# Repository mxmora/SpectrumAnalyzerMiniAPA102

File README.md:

# SpectrumAnalyzerMiniAPA102
SpectrumAnalyzerMiniAPA102

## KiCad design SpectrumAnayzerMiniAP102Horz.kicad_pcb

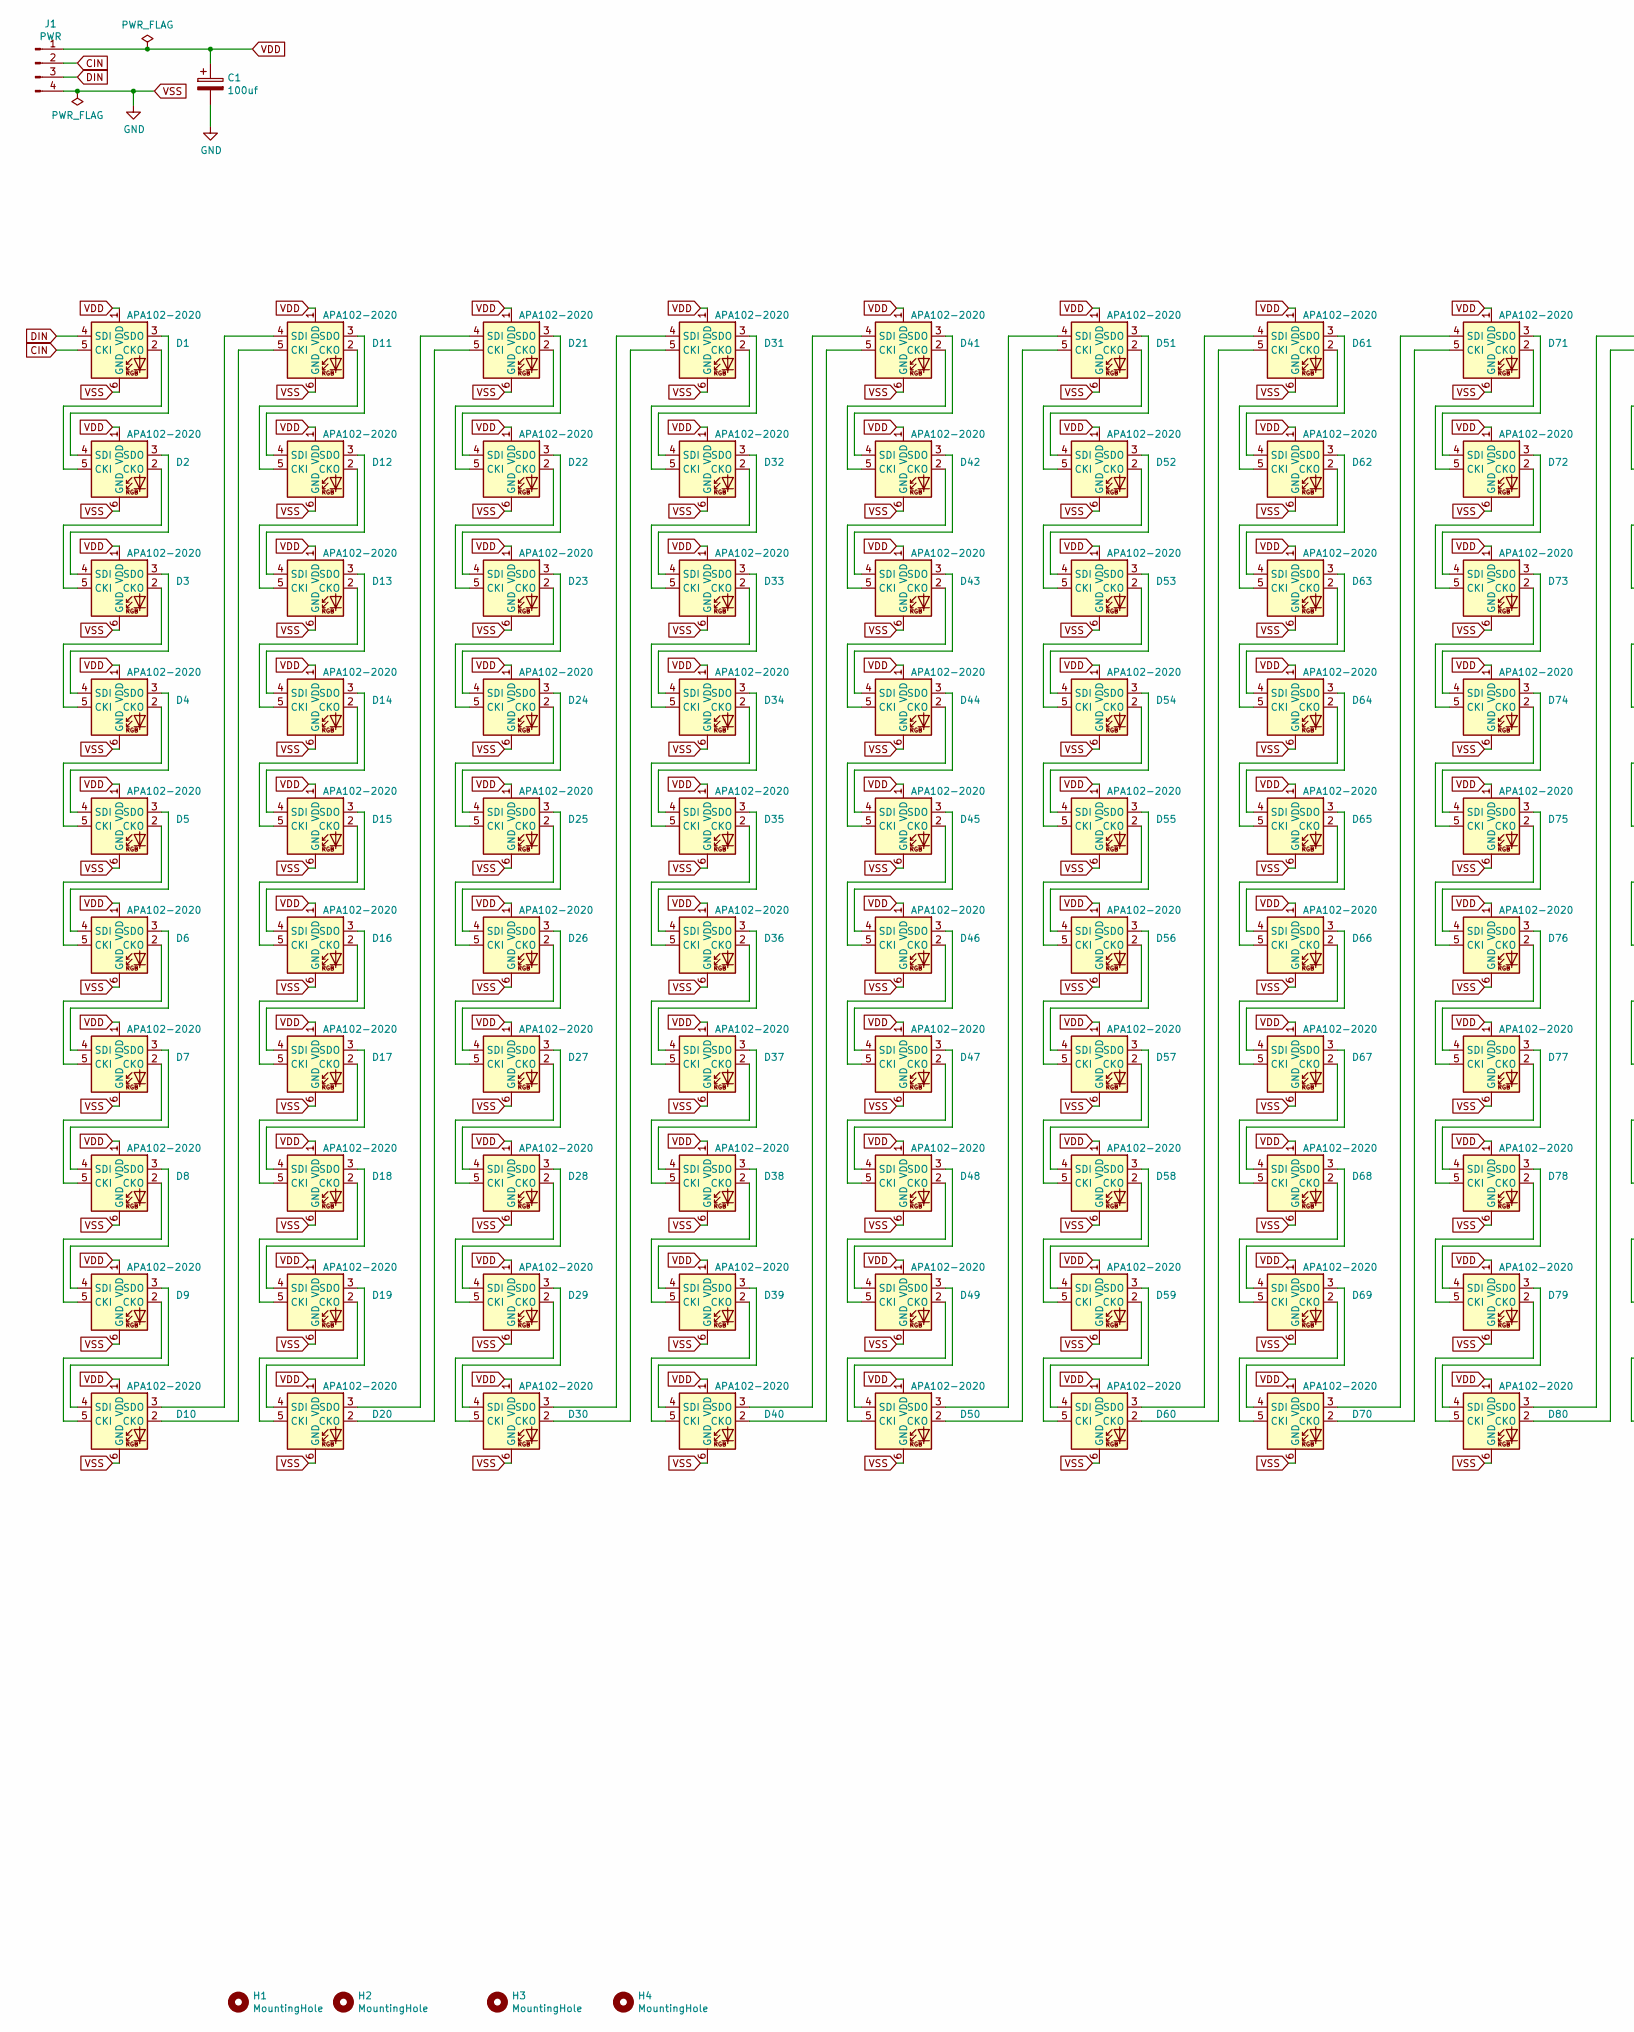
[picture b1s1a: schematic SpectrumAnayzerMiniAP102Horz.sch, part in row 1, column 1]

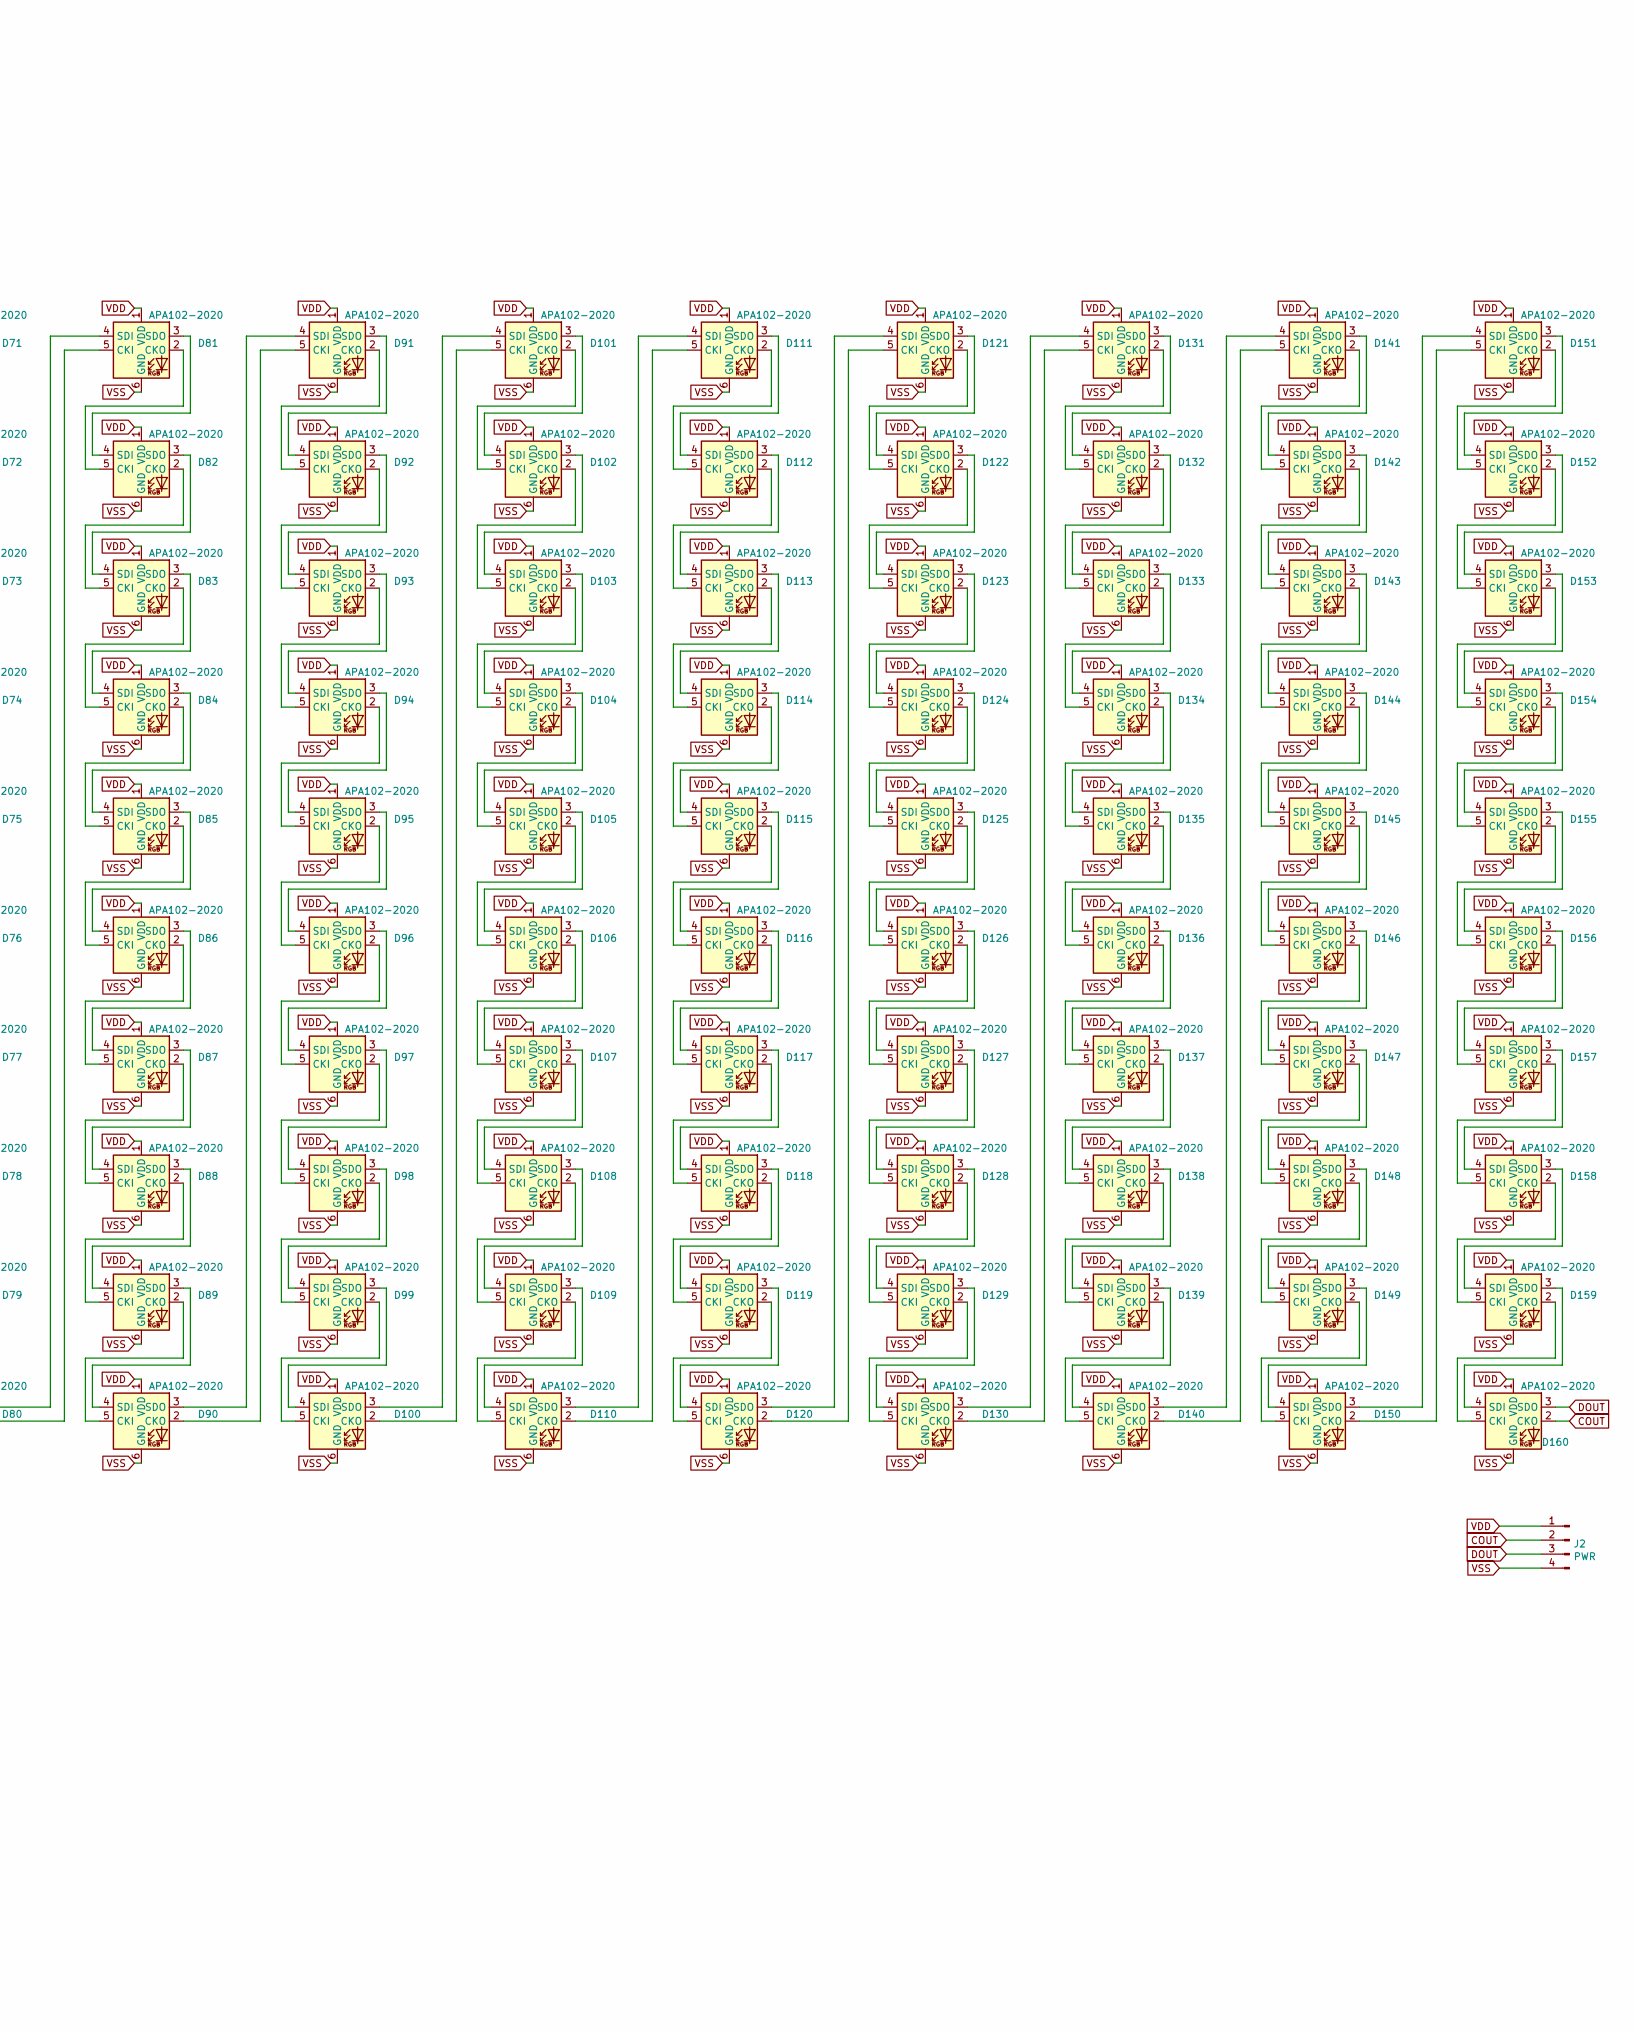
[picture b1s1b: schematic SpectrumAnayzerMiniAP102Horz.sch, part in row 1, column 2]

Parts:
C1: 100uf; CP_Radial_D5.0mm_P2.50mm
D1, D11, D21, D31, D41, D51, D61, D71, D81, D91, D101, D111, D121, D131, D141, D151: APA102-2020; LED-APA102-2020; LCSC C114586
D2, D3, D4, D5, D6, D7, D8, D9, D10, D12, D13, D14, D15, D16, D17, D18, D19, D20, D22, D23, D24, D25, D26, D27, D28, D29, D30, D32, D33, D34, D35, D36, D37, D38, D39, D40, D42, D43, D44, D45, D46, D47, D48, D49, D50, D52, D53, D54, D55, D56, D57, D58, D59, D60, D62, D63, D64, D65, D66, D67, D68, D69, D70, D72, D73, D74, D75, D76, D77, D78, D79, D80, D82, D83, D84, D85, D86, D87, D88, D89, D90, D92, D93, D94, D95, D96, D97, D98, D99, D100, D102, D103, D104, D105, D106, D107, D108, D109, D110, D112, D113, D114, D115, D116, D117, D118, D119, D120, D122, D123, D124, D125, D126, D127, D128, D129, D130, D132, D133, D134, D135, D136, D137, D138, D139, D140, D142, D143, D144, D145, D146, D147, D148, D149, D150, D152, D153, D154, D155, D156, D157, D158, D159, D160: APA102-2020; LED-APA102-2020
H1, H2, H3, H4: MountingHole; MountingHole_2.5mm
J1, J2: PWR; PinHeader_1x04_P2.54mm_Vertical

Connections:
CIN: D1.5 (CKI), J1.2
COUT: D160.2 (CKO), J2.2
DIN: D1.4 (SDI), J1.3
DOUT: D160.3 (SDO), J2.3
unnamed: D1.2 (CKO), D2.5 (CKI)
unnamed: D1.3 (SDO), D2.4 (SDI)
unnamed: D2.2 (CKO), D3.5 (CKI)
unnamed: D2.3 (SDO), D3.4 (SDI)
unnamed: D3.2 (CKO), D4.5 (CKI)
unnamed: D3.3 (SDO), D4.4 (SDI)
unnamed: D4.2 (CKO), D5.5 (CKI)
unnamed: D4.3 (SDO), D5.4 (SDI)
unnamed: D5.2 (CKO), D6.5 (CKI)
unnamed: D5.3 (SDO), D6.4 (SDI)
unnamed: D6.2 (CKO), D7.5 (CKI)
unnamed: D6.3 (SDO), D7.4 (SDI)
unnamed: D7.2 (CKO), D8.5 (CKI)
unnamed: D7.3 (SDO), D8.4 (SDI)
unnamed: D8.2 (CKO), D9.5 (CKI)
unnamed: D8.3 (SDO), D9.4 (SDI)
unnamed: D10.2 (CKO), D11.5 (CKI)
unnamed: D10.3 (SDO), D11.4 (SDI)
unnamed: D9.3 (SDO), D10.4 (SDI)
unnamed: D9.2 (CKO), D10.5 (CKI)
unnamed: D11.2 (CKO), D12.5 (CKI)
unnamed: D11.3 (SDO), D12.4 (SDI)
unnamed: D12.2 (CKO), D13.5 (CKI)
unnamed: D12.3 (SDO), D13.4 (SDI)
unnamed: D13.2 (CKO), D14.5 (CKI)
unnamed: D13.3 (SDO), D14.4 (SDI)
unnamed: D14.2 (CKO), D15.5 (CKI)
unnamed: D14.3 (SDO), D15.4 (SDI)
unnamed: D15.2 (CKO), D16.5 (CKI)
unnamed: D15.3 (SDO), D16.4 (SDI)
unnamed: D16.2 (CKO), D17.5 (CKI)
unnamed: D16.3 (SDO), D17.4 (SDI)
unnamed: D17.2 (CKO), D18.5 (CKI)
unnamed: D17.3 (SDO), D18.4 (SDI)
unnamed: D18.2 (CKO), D19.5 (CKI)
unnamed: D18.3 (SDO), D19.4 (SDI)
unnamed: D19.2 (CKO), D20.5 (CKI)
unnamed: D19.3 (SDO), D20.4 (SDI)
unnamed: D20.2 (CKO), D21.5 (CKI)
unnamed: D20.3 (SDO), D21.4 (SDI)
unnamed: D21.2 (CKO), D22.5 (CKI)
unnamed: D21.3 (SDO), D22.4 (SDI)
unnamed: D22.2 (CKO), D23.5 (CKI)
unnamed: D22.3 (SDO), D23.4 (SDI)
unnamed: D23.2 (CKO), D24.5 (CKI)
unnamed: D23.3 (SDO), D24.4 (SDI)
unnamed: D24.2 (CKO), D25.5 (CKI)
unnamed: D24.3 (SDO), D25.4 (SDI)
unnamed: D25.2 (CKO), D26.5 (CKI)
unnamed: D25.3 (SDO), D26.4 (SDI)
unnamed: D26.2 (CKO), D27.5 (CKI)
unnamed: D26.3 (SDO), D27.4 (SDI)
unnamed: D27.2 (CKO), D28.5 (CKI)
unnamed: D27.3 (SDO), D28.4 (SDI)
unnamed: D28.2 (CKO), D29.5 (CKI)
unnamed: D28.3 (SDO), D29.4 (SDI)
unnamed: D29.2 (CKO), D30.5 (CKI)
unnamed: D29.3 (SDO), D30.4 (SDI)
unnamed: D30.2 (CKO), D31.5 (CKI)
unnamed: D30.3 (SDO), D31.4 (SDI)
unnamed: D31.2 (CKO), D32.5 (CKI)
unnamed: D31.3 (SDO), D32.4 (SDI)
unnamed: D32.2 (CKO), D33.5 (CKI)
unnamed: D32.3 (SDO), D33.4 (SDI)
unnamed: D33.2 (CKO), D34.5 (CKI)
unnamed: D33.3 (SDO), D34.4 (SDI)
unnamed: D34.2 (CKO), D35.5 (CKI)
unnamed: D34.3 (SDO), D35.4 (SDI)
unnamed: D35.2 (CKO), D36.5 (CKI)
unnamed: D35.3 (SDO), D36.4 (SDI)
unnamed: D36.2 (CKO), D37.5 (CKI)
unnamed: D36.3 (SDO), D37.4 (SDI)
unnamed: D37.2 (CKO), D38.5 (CKI)
unnamed: D37.3 (SDO), D38.4 (SDI)
unnamed: D38.2 (CKO), D39.5 (CKI)
unnamed: D38.3 (SDO), D39.4 (SDI)
unnamed: D39.2 (CKO), D40.5 (CKI)
unnamed: D39.3 (SDO), D40.4 (SDI)
unnamed: D40.2 (CKO), D41.5 (CKI)
unnamed: D40.3 (SDO), D41.4 (SDI)
unnamed: D41.2 (CKO), D42.5 (CKI)
unnamed: D41.3 (SDO), D42.4 (SDI)
unnamed: D42.2 (CKO), D43.5 (CKI)
unnamed: D42.3 (SDO), D43.4 (SDI)
unnamed: D43.2 (CKO), D44.5 (CKI)
unnamed: D43.3 (SDO), D44.4 (SDI)
unnamed: D44.2 (CKO), D45.5 (CKI)
unnamed: D44.3 (SDO), D45.4 (SDI)
unnamed: D45.2 (CKO), D46.5 (CKI)
unnamed: D45.3 (SDO), D46.4 (SDI)
unnamed: D46.2 (CKO), D47.5 (CKI)
unnamed: D46.3 (SDO), D47.4 (SDI)
unnamed: D47.2 (CKO), D48.5 (CKI)
unnamed: D47.3 (SDO), D48.4 (SDI)
unnamed: D48.2 (CKO), D49.5 (CKI)
unnamed: D48.3 (SDO), D49.4 (SDI)
unnamed: D49.2 (CKO), D50.5 (CKI)
unnamed: D49.3 (SDO), D50.4 (SDI)
unnamed: D50.2 (CKO), D51.5 (CKI)
unnamed: D50.3 (SDO), D51.4 (SDI)
unnamed: D51.2 (CKO), D52.5 (CKI)
unnamed: D51.3 (SDO), D52.4 (SDI)
unnamed: D52.2 (CKO), D53.5 (CKI)
unnamed: D52.3 (SDO), D53.4 (SDI)
unnamed: D53.2 (CKO), D54.5 (CKI)
unnamed: D53.3 (SDO), D54.4 (SDI)
unnamed: D54.2 (CKO), D55.5 (CKI)
unnamed: D54.3 (SDO), D55.4 (SDI)
unnamed: D55.2 (CKO), D56.5 (CKI)
unnamed: D55.3 (SDO), D56.4 (SDI)
unnamed: D56.2 (CKO), D57.5 (CKI)
unnamed: D56.3 (SDO), D57.4 (SDI)
unnamed: D57.2 (CKO), D58.5 (CKI)
unnamed: D57.3 (SDO), D58.4 (SDI)
unnamed: D58.2 (CKO), D59.5 (CKI)
unnamed: D58.3 (SDO), D59.4 (SDI)
unnamed: D59.2 (CKO), D60.5 (CKI)
unnamed: D59.3 (SDO), D60.4 (SDI)
unnamed: D60.2 (CKO), D61.5 (CKI)
unnamed: D60.3 (SDO), D61.4 (SDI)
unnamed: D61.2 (CKO), D62.5 (CKI)
unnamed: D61.3 (SDO), D62.4 (SDI)
unnamed: D62.2 (CKO), D63.5 (CKI)
unnamed: D62.3 (SDO), D63.4 (SDI)
unnamed: D63.2 (CKO), D64.5 (CKI)
unnamed: D63.3 (SDO), D64.4 (SDI)
unnamed: D64.2 (CKO), D65.5 (CKI)
unnamed: D64.3 (SDO), D65.4 (SDI)
unnamed: D65.2 (CKO), D66.5 (CKI)
unnamed: D65.3 (SDO), D66.4 (SDI)
unnamed: D66.2 (CKO), D67.5 (CKI)
unnamed: D66.3 (SDO), D67.4 (SDI)
unnamed: D67.2 (CKO), D68.5 (CKI)
unnamed: D67.3 (SDO), D68.4 (SDI)
unnamed: D68.2 (CKO), D69.5 (CKI)
unnamed: D68.3 (SDO), D69.4 (SDI)
unnamed: D69.2 (CKO), D70.5 (CKI)
unnamed: D69.3 (SDO), D70.4 (SDI)
unnamed: D70.2 (CKO), D71.5 (CKI)
unnamed: D70.3 (SDO), D71.4 (SDI)
unnamed: D71.2 (CKO), D72.5 (CKI)
unnamed: D71.3 (SDO), D72.4 (SDI)
unnamed: D72.2 (CKO), D73.5 (CKI)
unnamed: D72.3 (SDO), D73.4 (SDI)
unnamed: D73.2 (CKO), D74.5 (CKI)
unnamed: D73.3 (SDO), D74.4 (SDI)
unnamed: D74.2 (CKO), D75.5 (CKI)
unnamed: D74.3 (SDO), D75.4 (SDI)
unnamed: D75.2 (CKO), D76.5 (CKI)
unnamed: D75.3 (SDO), D76.4 (SDI)
unnamed: D76.2 (CKO), D77.5 (CKI)
unnamed: D76.3 (SDO), D77.4 (SDI)
unnamed: D77.2 (CKO), D78.5 (CKI)
unnamed: D77.3 (SDO), D78.4 (SDI)
unnamed: D78.2 (CKO), D79.5 (CKI)
unnamed: D78.3 (SDO), D79.4 (SDI)
unnamed: D79.2 (CKO), D80.5 (CKI)
unnamed: D79.3 (SDO), D80.4 (SDI)
unnamed: D80.2 (CKO), D81.5 (CKI)
unnamed: D80.3 (SDO), D81.4 (SDI)
unnamed: D81.2 (CKO), D82.5 (CKI)
unnamed: D81.3 (SDO), D82.4 (SDI)
unnamed: D82.2 (CKO), D83.5 (CKI)
unnamed: D82.3 (SDO), D83.4 (SDI)
unnamed: D83.2 (CKO), D84.5 (CKI)
unnamed: D83.3 (SDO), D84.4 (SDI)
unnamed: D84.2 (CKO), D85.5 (CKI)
unnamed: D84.3 (SDO), D85.4 (SDI)
unnamed: D85.2 (CKO), D86.5 (CKI)
unnamed: D85.3 (SDO), D86.4 (SDI)
unnamed: D86.2 (CKO), D87.5 (CKI)
unnamed: D86.3 (SDO), D87.4 (SDI)
unnamed: D87.2 (CKO), D88.5 (CKI)
unnamed: D87.3 (SDO), D88.4 (SDI)
unnamed: D88.2 (CKO), D89.5 (CKI)
unnamed: D88.3 (SDO), D89.4 (SDI)
unnamed: D89.2 (CKO), D90.5 (CKI)
unnamed: D89.3 (SDO), D90.4 (SDI)
unnamed: D90.2 (CKO), D91.5 (CKI)
unnamed: D90.3 (SDO), D91.4 (SDI)
unnamed: D91.2 (CKO), D92.5 (CKI)
unnamed: D91.3 (SDO), D92.4 (SDI)
unnamed: D92.2 (CKO), D93.5 (CKI)
unnamed: D92.3 (SDO), D93.4 (SDI)
unnamed: D93.2 (CKO), D94.5 (CKI)
unnamed: D93.3 (SDO), D94.4 (SDI)
unnamed: D94.2 (CKO), D95.5 (CKI)
unnamed: D94.3 (SDO), D95.4 (SDI)
unnamed: D95.2 (CKO), D96.5 (CKI)
unnamed: D95.3 (SDO), D96.4 (SDI)
unnamed: D96.2 (CKO), D97.5 (CKI)
unnamed: D96.3 (SDO), D97.4 (SDI)
unnamed: D97.2 (CKO), D98.5 (CKI)
unnamed: D97.3 (SDO), D98.4 (SDI)
unnamed: D98.2 (CKO), D99.5 (CKI)
unnamed: D98.3 (SDO), D99.4 (SDI)
unnamed: D100.2 (CKO), D101.5 (CKI)
unnamed: D100.3 (SDO), D101.4 (SDI)
unnamed: D99.3 (SDO), D100.4 (SDI)
unnamed: D99.2 (CKO), D100.5 (CKI)
unnamed: D101.2 (CKO), D102.5 (CKI)
unnamed: D101.3 (SDO), D102.4 (SDI)
unnamed: D102.2 (CKO), D103.5 (CKI)
unnamed: D102.3 (SDO), D103.4 (SDI)
unnamed: D103.2 (CKO), D104.5 (CKI)
unnamed: D103.3 (SDO), D104.4 (SDI)
unnamed: D104.2 (CKO), D105.5 (CKI)
unnamed: D104.3 (SDO), D105.4 (SDI)
unnamed: D105.2 (CKO), D106.5 (CKI)
unnamed: D105.3 (SDO), D106.4 (SDI)
unnamed: D106.2 (CKO), D107.5 (CKI)
unnamed: D106.3 (SDO), D107.4 (SDI)
unnamed: D107.2 (CKO), D108.5 (CKI)
unnamed: D107.3 (SDO), D108.4 (SDI)
unnamed: D108.2 (CKO), D109.5 (CKI)
unnamed: D108.3 (SDO), D109.4 (SDI)
unnamed: D109.2 (CKO), D110.5 (CKI)
unnamed: D109.3 (SDO), D110.4 (SDI)
unnamed: D110.2 (CKO), D111.5 (CKI)
unnamed: D110.3 (SDO), D111.4 (SDI)
unnamed: D111.2 (CKO), D112.5 (CKI)
unnamed: D111.3 (SDO), D112.4 (SDI)
unnamed: D112.2 (CKO), D113.5 (CKI)
unnamed: D112.3 (SDO), D113.4 (SDI)
unnamed: D113.2 (CKO), D114.5 (CKI)
unnamed: D113.3 (SDO), D114.4 (SDI)
unnamed: D114.2 (CKO), D115.5 (CKI)
unnamed: D114.3 (SDO), D115.4 (SDI)
unnamed: D115.2 (CKO), D116.5 (CKI)
unnamed: D115.3 (SDO), D116.4 (SDI)
unnamed: D116.2 (CKO), D117.5 (CKI)
unnamed: D116.3 (SDO), D117.4 (SDI)
unnamed: D117.2 (CKO), D118.5 (CKI)
unnamed: D117.3 (SDO), D118.4 (SDI)
unnamed: D118.2 (CKO), D119.5 (CKI)
unnamed: D118.3 (SDO), D119.4 (SDI)
unnamed: D119.2 (CKO), D120.5 (CKI)
unnamed: D119.3 (SDO), D120.4 (SDI)
unnamed: D120.2 (CKO), D121.5 (CKI)
unnamed: D120.3 (SDO), D121.4 (SDI)
unnamed: D121.2 (CKO), D122.5 (CKI)
unnamed: D121.3 (SDO), D122.4 (SDI)
unnamed: D122.2 (CKO), D123.5 (CKI)
unnamed: D122.3 (SDO), D123.4 (SDI)
unnamed: D123.2 (CKO), D124.5 (CKI)
unnamed: D123.3 (SDO), D124.4 (SDI)
unnamed: D124.2 (CKO), D125.5 (CKI)
unnamed: D124.3 (SDO), D125.4 (SDI)
unnamed: D125.2 (CKO), D126.5 (CKI)
unnamed: D125.3 (SDO), D126.4 (SDI)
unnamed: D126.2 (CKO), D127.5 (CKI)
unnamed: D126.3 (SDO), D127.4 (SDI)
unnamed: D127.2 (CKO), D128.5 (CKI)
unnamed: D127.3 (SDO), D128.4 (SDI)
unnamed: D128.2 (CKO), D129.5 (CKI)
unnamed: D128.3 (SDO), D129.4 (SDI)
unnamed: D129.2 (CKO), D130.5 (CKI)
unnamed: D129.3 (SDO), D130.4 (SDI)
unnamed: D130.2 (CKO), D131.5 (CKI)
unnamed: D130.3 (SDO), D131.4 (SDI)
unnamed: D131.2 (CKO), D132.5 (CKI)
unnamed: D131.3 (SDO), D132.4 (SDI)
unnamed: D132.2 (CKO), D133.5 (CKI)
unnamed: D132.3 (SDO), D133.4 (SDI)
unnamed: D133.2 (CKO), D134.5 (CKI)
unnamed: D133.3 (SDO), D134.4 (SDI)
unnamed: D134.2 (CKO), D135.5 (CKI)
unnamed: D134.3 (SDO), D135.4 (SDI)
unnamed: D135.2 (CKO), D136.5 (CKI)
unnamed: D135.3 (SDO), D136.4 (SDI)
unnamed: D136.2 (CKO), D137.5 (CKI)
unnamed: D136.3 (SDO), D137.4 (SDI)
unnamed: D137.2 (CKO), D138.5 (CKI)
unnamed: D137.3 (SDO), D138.4 (SDI)
unnamed: D138.2 (CKO), D139.5 (CKI)
unnamed: D138.3 (SDO), D139.4 (SDI)
unnamed: D139.2 (CKO), D140.5 (CKI)
unnamed: D139.3 (SDO), D140.4 (SDI)
unnamed: D140.2 (CKO), D141.5 (CKI)
unnamed: D140.3 (SDO), D141.4 (SDI)
unnamed: D141.2 (CKO), D142.5 (CKI)
unnamed: D141.3 (SDO), D142.4 (SDI)
unnamed: D142.2 (CKO), D143.5 (CKI)
unnamed: D142.3 (SDO), D143.4 (SDI)
unnamed: D143.2 (CKO), D144.5 (CKI)
unnamed: D143.3 (SDO), D144.4 (SDI)
unnamed: D144.2 (CKO), D145.5 (CKI)
unnamed: D144.3 (SDO), D145.4 (SDI)
unnamed: D145.2 (CKO), D146.5 (CKI)
unnamed: D145.3 (SDO), D146.4 (SDI)
unnamed: D146.2 (CKO), D147.5 (CKI)
unnamed: D146.3 (SDO), D147.4 (SDI)
unnamed: D147.2 (CKO), D148.5 (CKI)
unnamed: D147.3 (SDO), D148.4 (SDI)
unnamed: D148.2 (CKO), D149.5 (CKI)
unnamed: D148.3 (SDO), D149.4 (SDI)
unnamed: D149.2 (CKO), D150.5 (CKI)
unnamed: D149.3 (SDO), D150.4 (SDI)
unnamed: D150.2 (CKO), D151.5 (CKI)
unnamed: D150.3 (SDO), D151.4 (SDI)
unnamed: D151.2 (CKO), D152.5 (CKI)
unnamed: D151.3 (SDO), D152.4 (SDI)
unnamed: D152.2 (CKO), D153.5 (CKI)
unnamed: D152.3 (SDO), D153.4 (SDI)
unnamed: D153.2 (CKO), D154.5 (CKI)
unnamed: D153.3 (SDO), D154.4 (SDI)
unnamed: D154.2 (CKO), D155.5 (CKI)
unnamed: D154.3 (SDO), D155.4 (SDI)
unnamed: D155.2 (CKO), D156.5 (CKI)
unnamed: D155.3 (SDO), D156.4 (SDI)
unnamed: D156.2 (CKO), D157.5 (CKI)
unnamed: D156.3 (SDO), D157.4 (SDI)
unnamed: D157.2 (CKO), D158.5 (CKI)
unnamed: D157.3 (SDO), D158.4 (SDI)
unnamed: D158.2 (CKO), D159.5 (CKI)
unnamed: D158.3 (SDO), D159.4 (SDI)
unnamed: D159.2 (CKO), D160.5 (CKI)
unnamed: D159.3 (SDO), D160.4 (SDI)
VDD: C1.1, D1.1 (VDD), D2.1 (VDD), D3.1 (VDD), D4.1 (VDD), D5.1 (VDD), D6.1 (VDD), D7.1 (VDD), D8.1 (VDD), D9.1 (VDD), D10.1 (VDD), D11.1 (VDD), D12.1 (VDD), D13.1 (VDD), D14.1 (VDD), D15.1 (VDD), D16.1 (VDD), D17.1 (VDD), D18.1 (VDD), D19.1 (VDD), D20.1 (VDD), D21.1 (VDD), D22.1 (VDD), D23.1 (VDD), D24.1 (VDD), D25.1 (VDD), D26.1 (VDD), D27.1 (VDD), D28.1 (VDD), D29.1 (VDD), D30.1 (VDD), D31.1 (VDD), D32.1 (VDD), D33.1 (VDD), D34.1 (VDD), D35.1 (VDD), D36.1 (VDD), D37.1 (VDD), D38.1 (VDD), D39.1 (VDD), D40.1 (VDD), D41.1 (VDD), D42.1 (VDD), D43.1 (VDD), D44.1 (VDD), D45.1 (VDD), D46.1 (VDD), D47.1 (VDD), D48.1 (VDD), D49.1 (VDD), D50.1 (VDD), D51.1 (VDD), D52.1 (VDD), D53.1 (VDD), D54.1 (VDD), D55.1 (VDD), D56.1 (VDD), D57.1 (VDD), D58.1 (VDD), D59.1 (VDD), D60.1 (VDD), D61.1 (VDD), D62.1 (VDD), D63.1 (VDD), D64.1 (VDD), D65.1 (VDD), D66.1 (VDD), D67.1 (VDD), D68.1 (VDD), D69.1 (VDD), D70.1 (VDD), D71.1 (VDD), D72.1 (VDD), D73.1 (VDD), D74.1 (VDD), D75.1 (VDD), D76.1 (VDD), D77.1 (VDD), D78.1 (VDD), D79.1 (VDD), D80.1 (VDD), D81.1 (VDD), D82.1 (VDD), D83.1 (VDD), D84.1 (VDD), D85.1 (VDD), D86.1 (VDD), D87.1 (VDD), D88.1 (VDD), D89.1 (VDD), D90.1 (VDD), D91.1 (VDD), D92.1 (VDD), D93.1 (VDD), D94.1 (VDD), D95.1 (VDD), D96.1 (VDD), D97.1 (VDD), D98.1 (VDD), D99.1 (VDD), D100.1 (VDD), D101.1 (VDD), D102.1 (VDD), D103.1 (VDD), D104.1 (VDD), D105.1 (VDD), D106.1 (VDD), D107.1 (VDD), D108.1 (VDD), D109.1 (VDD), D110.1 (VDD), D111.1 (VDD), D112.1 (VDD), D113.1 (VDD), D114.1 (VDD), D115.1 (VDD), D116.1 (VDD), D117.1 (VDD), D118.1 (VDD), D119.1 (VDD), D120.1 (VDD), D121.1 (VDD), D122.1 (VDD), D123.1 (VDD), D124.1 (VDD), D125.1 (VDD), D126.1 (VDD), D127.1 (VDD), D128.1 (VDD), D129.1 (VDD), D130.1 (VDD), D131.1 (VDD), D132.1 (VDD), D133.1 (VDD), D134.1 (VDD), D135.1 (VDD), D136.1 (VDD), D137.1 (VDD), D138.1 (VDD), D139.1 (VDD), D140.1 (VDD), D141.1 (VDD), D142.1 (VDD), D143.1 (VDD), D144.1 (VDD), D145.1 (VDD), D146.1 (VDD), D147.1 (VDD), D148.1 (VDD), D149.1 (VDD), D150.1 (VDD), D151.1 (VDD), D152.1 (VDD), D153.1 (VDD), D154.1 (VDD), D155.1 (VDD), D156.1 (VDD), D157.1 (VDD), D158.1 (VDD), D159.1 (VDD), D160.1 (VDD), J1.1, J2.1
VSS: C1.2, D1.6 (GND), D2.6 (GND), D3.6 (GND), D4.6 (GND), D5.6 (GND), D6.6 (GND), D7.6 (GND), D8.6 (GND), D9.6 (GND), D10.6 (GND), D11.6 (GND), D12.6 (GND), D13.6 (GND), D14.6 (GND), D15.6 (GND), D16.6 (GND), D17.6 (GND), D18.6 (GND), D19.6 (GND), D20.6 (GND), D21.6 (GND), D22.6 (GND), D23.6 (GND), D24.6 (GND), D25.6 (GND), D26.6 (GND), D27.6 (GND), D28.6 (GND), D29.6 (GND), D30.6 (GND), D31.6 (GND), D32.6 (GND), D33.6 (GND), D34.6 (GND), D35.6 (GND), D36.6 (GND), D37.6 (GND), D38.6 (GND), D39.6 (GND), D40.6 (GND), D41.6 (GND), D42.6 (GND), D43.6 (GND), D44.6 (GND), D45.6 (GND), D46.6 (GND), D47.6 (GND), D48.6 (GND), D49.6 (GND), D50.6 (GND), D51.6 (GND), D52.6 (GND), D53.6 (GND), D54.6 (GND), D55.6 (GND), D56.6 (GND), D57.6 (GND), D58.6 (GND), D59.6 (GND), D60.6 (GND), D61.6 (GND), D62.6 (GND), D63.6 (GND), D64.6 (GND), D65.6 (GND), D66.6 (GND), D67.6 (GND), D68.6 (GND), D69.6 (GND), D70.6 (GND), D71.6 (GND), D72.6 (GND), D73.6 (GND), D74.6 (GND), D75.6 (GND), D76.6 (GND), D77.6 (GND), D78.6 (GND), D79.6 (GND), D80.6 (GND), D81.6 (GND), D82.6 (GND), D83.6 (GND), D84.6 (GND), D85.6 (GND), D86.6 (GND), D87.6 (GND), D88.6 (GND), D89.6 (GND), D90.6 (GND), D91.6 (GND), D92.6 (GND), D93.6 (GND), D94.6 (GND), D95.6 (GND), D96.6 (GND), D97.6 (GND), D98.6 (GND), D99.6 (GND), D100.6 (GND), D101.6 (GND), D102.6 (GND), D103.6 (GND), D104.6 (GND), D105.6 (GND), D106.6 (GND), D107.6 (GND), D108.6 (GND), D109.6 (GND), D110.6 (GND), D111.6 (GND), D112.6 (GND), D113.6 (GND), D114.6 (GND), D115.6 (GND), D116.6 (GND), D117.6 (GND), D118.6 (GND), D119.6 (GND), D120.6 (GND), D121.6 (GND), D122.6 (GND), D123.6 (GND), D124.6 (GND), D125.6 (GND), D126.6 (GND), D127.6 (GND), D128.6 (GND), D129.6 (GND), D130.6 (GND), D131.6 (GND), D132.6 (GND), D133.6 (GND), D134.6 (GND), D135.6 (GND), D136.6 (GND), D137.6 (GND), D138.6 (GND), D139.6 (GND), D140.6 (GND), D141.6 (GND), D142.6 (GND), D143.6 (GND), D144.6 (GND), D145.6 (GND), D146.6 (GND), D147.6 (GND), D148.6 (GND), D149.6 (GND), D150.6 (GND), D151.6 (GND), D152.6 (GND), D153.6 (GND), D154.6 (GND), D155.6 (GND), D156.6 (GND), D157.6 (GND), D158.6 (GND), D159.6 (GND), D160.6 (GND), J1.4, J2.4

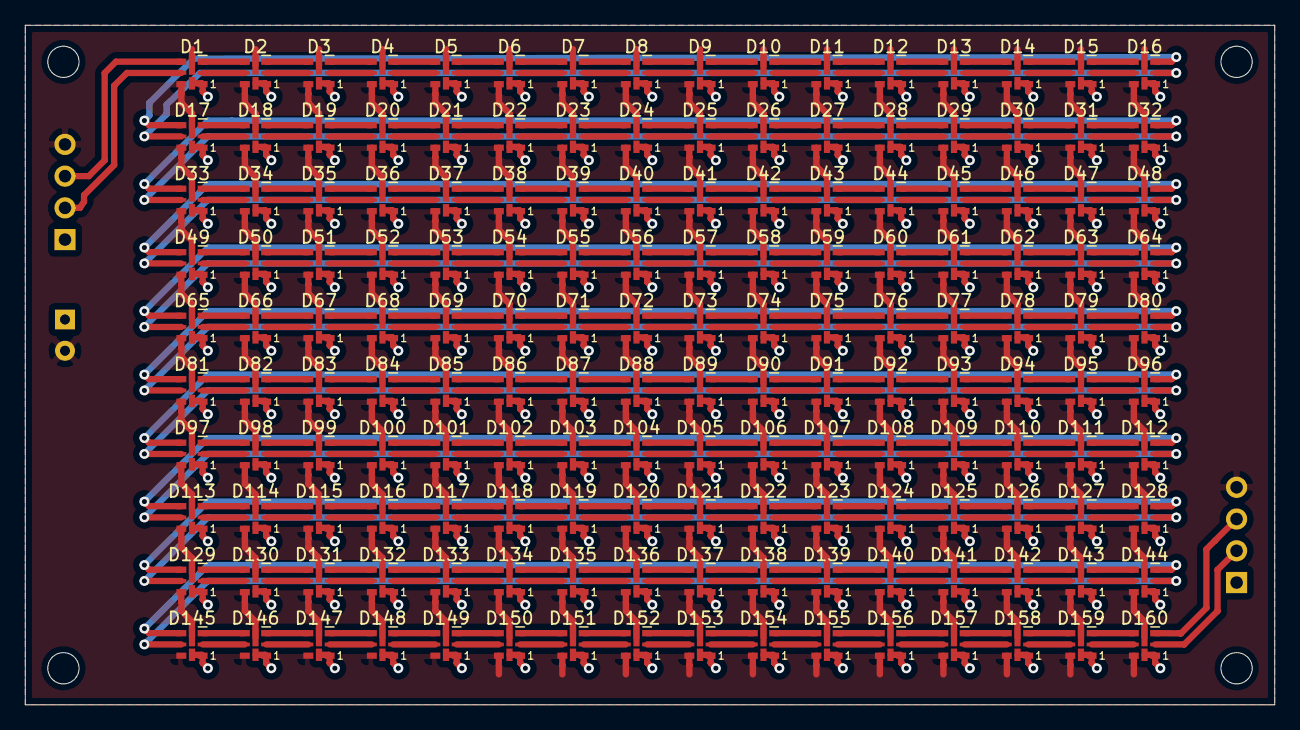
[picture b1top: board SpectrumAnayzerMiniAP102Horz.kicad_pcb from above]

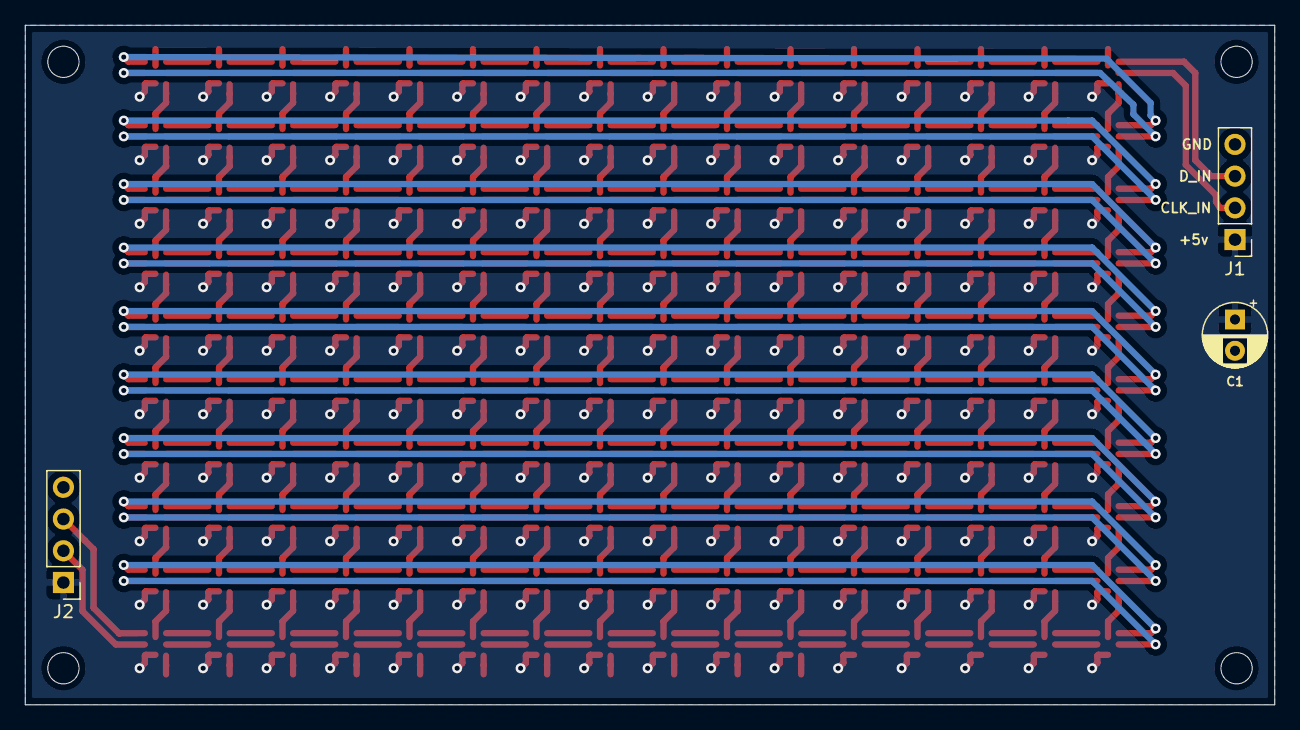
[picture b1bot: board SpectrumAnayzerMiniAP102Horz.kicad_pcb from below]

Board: 2 copper layers, 99.9 x 54.4 mm, 167 parts (3 on the bottom side), 324 nets.

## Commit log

2020-03-07 first check in
2020-03-08 finished layout
